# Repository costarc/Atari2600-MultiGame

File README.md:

# Atari 2600 MultiGame Cartridge

Bill of material
--
Bill of Material is in interactive mode - click on file https://github.com/costarc/Atari2600-MultiGame/blob/master/ibom.html (you may need to download to your local computer to see it properly)

## 📖 The Book

This project is **Chapter 6, "Atari 2600 MultiGame"**, in a book:

**Chips, Code, and Cartridges: Turn Curiosity into Creation with 13 Hands-On Projects, from 8-bit Classics to FPGAs**

It walks through thirteen of my own hardware and software projects, from 8-bit classics to FPGAs, for beginners and curious makers. Each chapter explains how one project works and how to build it, with colour diagrams and real code from its repository.

### 👉 [Get the book on Amazon](https://link.amazon/B013Yaq9y)

<sub>As an Amazon Associate, the author earns from qualifying purchases. Buying through this link
supports these projects at no extra cost to you.</sub>

# Description

This cartridge supports 2K and 4K games.
2K games must be 4K as well (two copies of the same file appended). For example, the followign two commands will (compatible with Mac OS, Linux and CygWin in windows) will create a 4kgame.bin file with two copies of the same 2kgame.bin:<br>
<code>
cat 2kgame.bin >  4kgame.bin<br>
cat 2kgame.bin >> 4kgame.bin<br>
</code>
<br>
The PCB supports 27C512 ROMs and EPROMS and can hold up to 16 games, switchable via the DIP Switch at the back of the cartridge.

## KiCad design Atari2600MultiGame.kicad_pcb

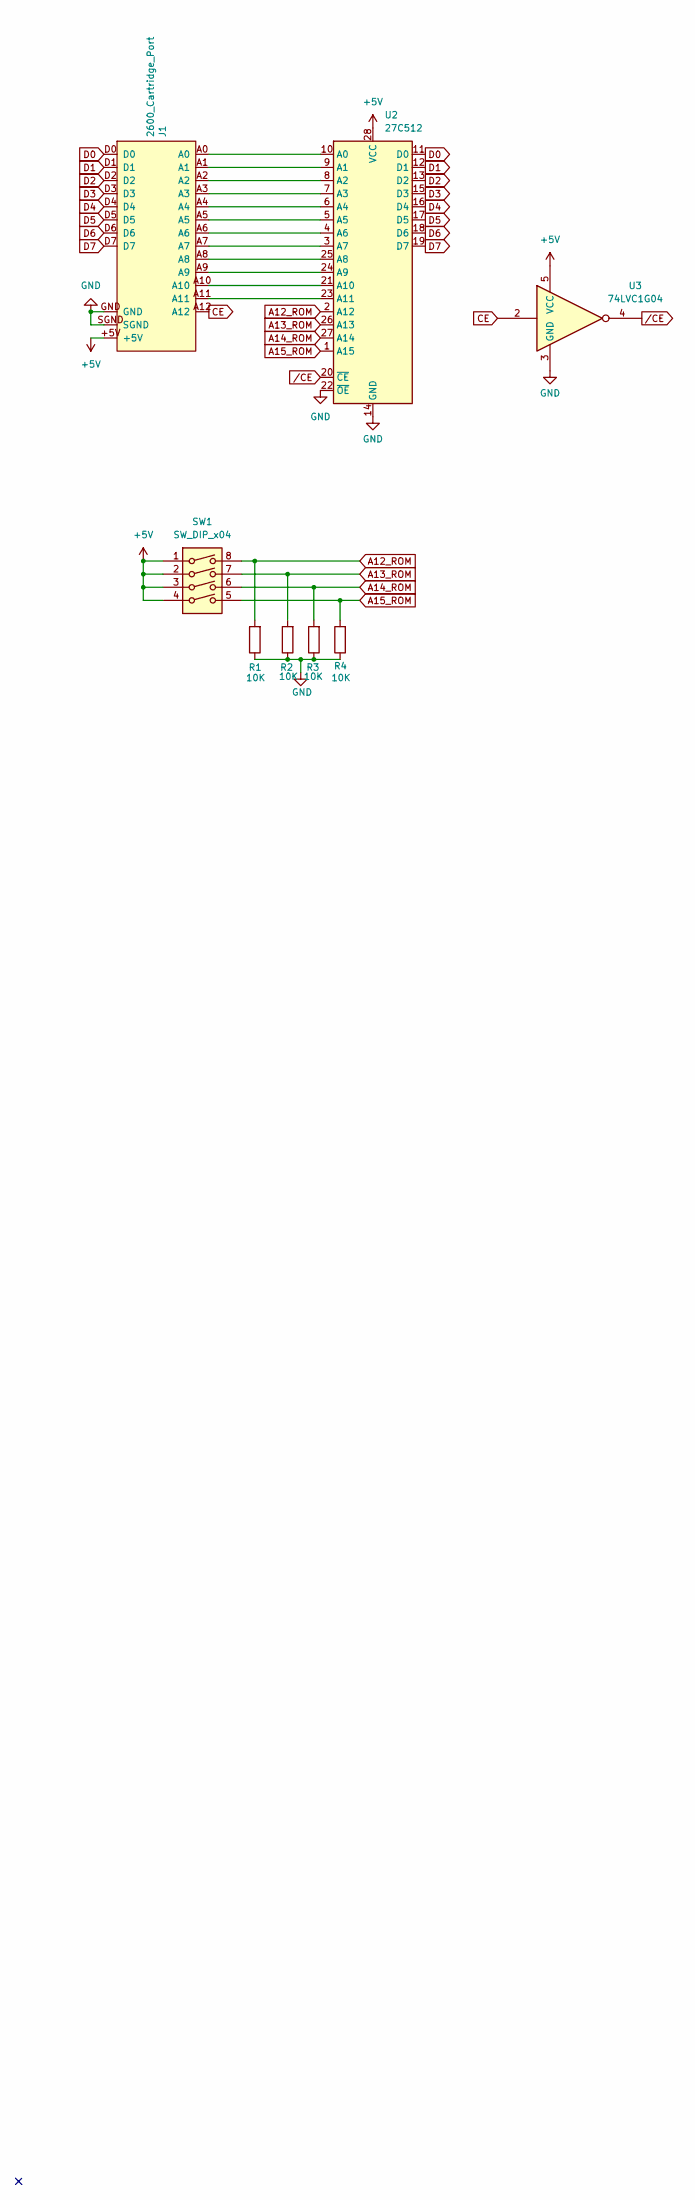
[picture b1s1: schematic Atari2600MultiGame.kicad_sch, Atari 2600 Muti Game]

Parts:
J1: 2600_Cartridge_Port
R1, R2, R3, R4: 10K; R_Axial_DIN0207_L6.3mm_D2.5mm_P7.62mm_Horizontal
SW1: SW_DIP_x04; SW_DIP_SPSTx04_Slide_6.7x11.72mm_W7.62mm_P2.54mm_LowProfile
U2: 27C512; DIP-28_W15.24mm
U3: 74LVC1G04; SOT-23-5_HandSoldering

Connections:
+5V: J1.+5V, SW1.1, SW1.2, SW1.3, SW1.4, U2.28 (VCC), U3.5 (VCC)
A12_ROM: R1.2, SW1.8, U2.2 (A12)
A13_ROM: R2.2, SW1.7, U2.26 (A13)
A14_ROM: R3.2, SW1.6, U2.27 (A14)
A15_ROM: R4.2, SW1.5, U2.1 (A15)
CE: J1.A12, U3.2
D0: J1.D0, U2.11 (D0)
D1: J1.D1, U2.12 (D1)
D2: J1.D2, U2.13 (D2)
D3: J1.D3, U2.15 (D3)
D4: J1.D4, U2.16 (D4)
D5: J1.D5, U2.17 (D5)
D6: J1.D6, U2.18 (D6)
D7: J1.D7, U2.19 (D7)
GND: J1.GND, J1.SGND, R1.1, R2.1, R3.1, R4.1, U2.14 (GND), U2.22 (~OE), U3.3 (GND)
unnamed: J1.A0, U2.10 (A0)
unnamed: J1.A1, U2.9 (A1)
unnamed: J1.A2, U2.8 (A2)
unnamed: J1.A3, U2.7 (A3)
unnamed: J1.A4, U2.6 (A4)
unnamed: J1.A5, U2.5 (A5)
unnamed: J1.A6, U2.4 (A6)
unnamed: J1.A7, U2.3 (A7)
unnamed: J1.A8, U2.25 (A8)
unnamed: J1.A9, U2.24 (A9)
unnamed: J1.A10, U2.21 (A10)
unnamed: J1.A11, U2.23 (A11)
/CE: U2.20 (~CE), U3.4

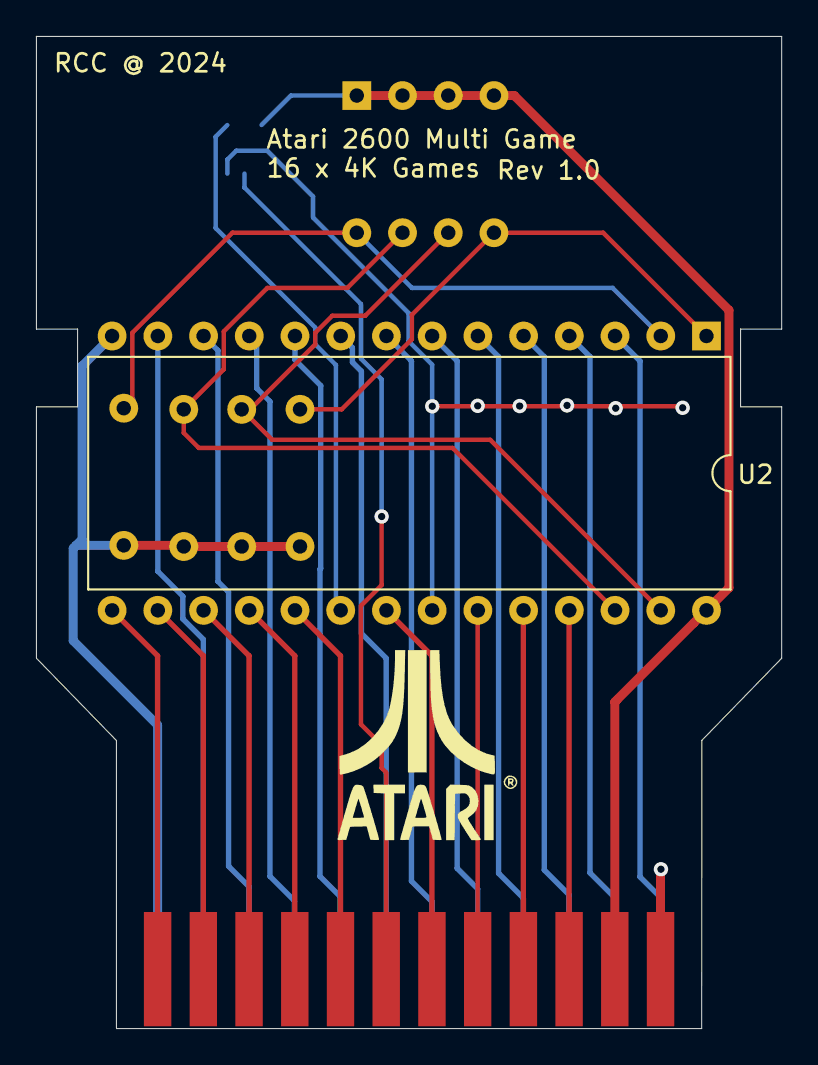
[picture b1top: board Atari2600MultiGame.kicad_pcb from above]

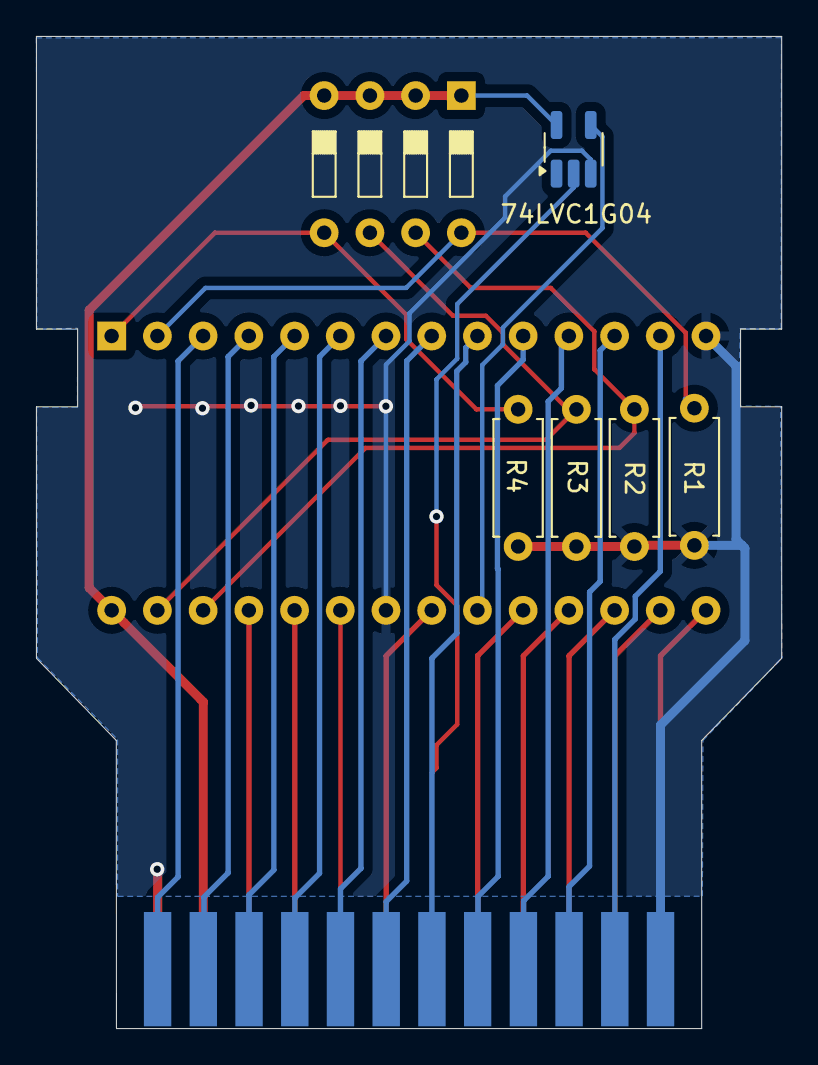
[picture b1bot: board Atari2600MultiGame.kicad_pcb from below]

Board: 2 copper layers, 41.4 x 55.1 mm, 8 parts (6 on the bottom side), 28 nets.

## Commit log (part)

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2024-06-19 Rev. 1.0 - Sent for Fabrication
2024-06-19 ibom
